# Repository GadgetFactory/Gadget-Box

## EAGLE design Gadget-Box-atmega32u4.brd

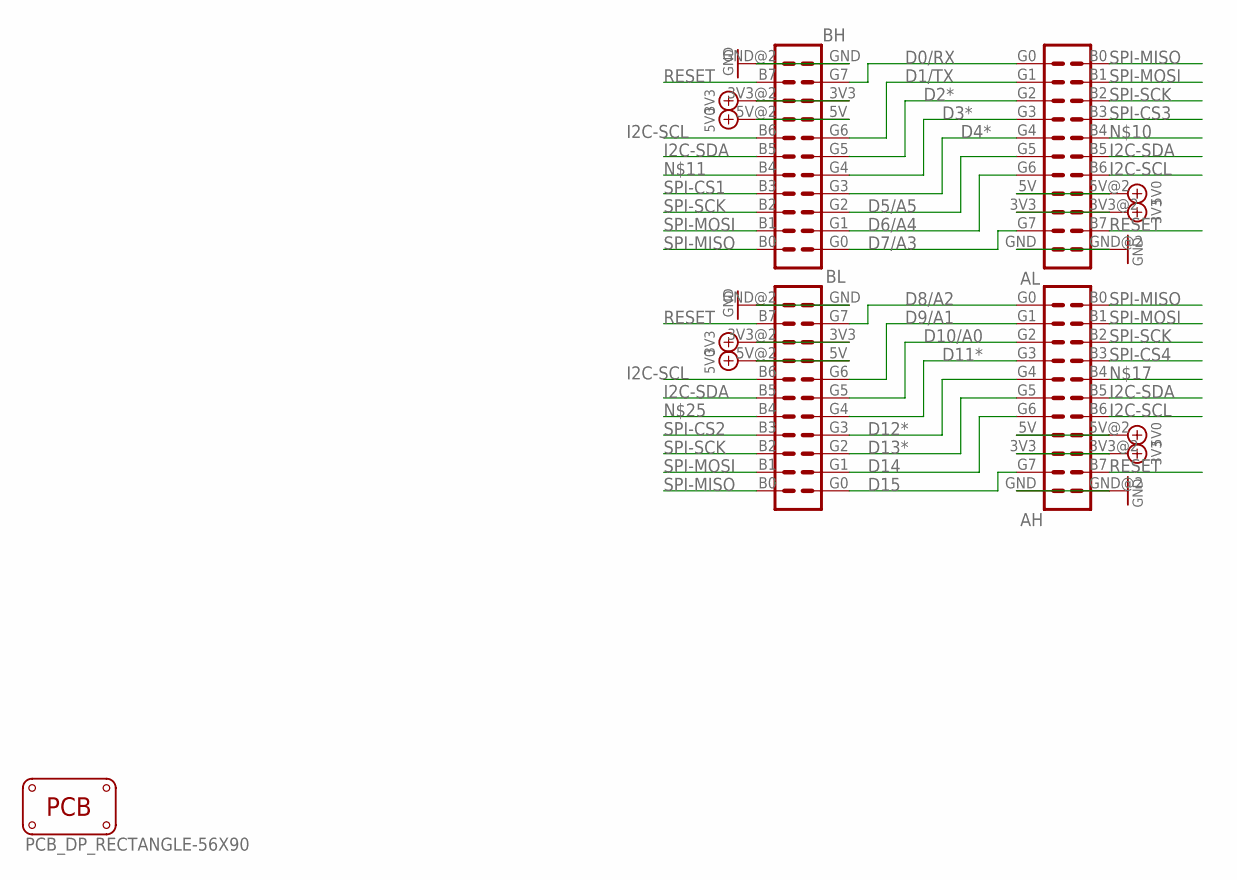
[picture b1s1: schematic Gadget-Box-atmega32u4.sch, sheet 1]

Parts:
AH: ECOGECOG_SLOT; ECOG
AL: ECOGECOG_SLOT; ECOG
BH: ECOGECOG_SLOT; ECOG
BL: ECOGECOG_SLOT; ECOG
PCB1: PCB_DP_RECTANGLE-56X90; DP9056_V1

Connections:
3V3: AH.3V3, AH.3V3@2 (3V3), AL.3V3, AL.3V3@2 (3V3), BH.3V3, BH.3V3@2 (3V3), BL.3V3, BL.3V3@2 (3V3); also elsewhere on the board
5V0: AH.5V, AH.5V@2 (5V), AL.5V, AL.5V@2 (5V), BH.5V, BH.5V@2 (5V), BL.5V, BL.5V@2 (5V); also elsewhere on the board
D0/RX: AL.G0, BH.G7; also elsewhere on the board
D1/TX: AL.G1, BH.G6; also elsewhere on the board
D2*: AL.G2, BH.G5; also elsewhere on the board
D3*: AL.G3, BH.G4; also elsewhere on the board
D4*: AL.G4, BH.G3; also elsewhere on the board
D5/A5: AL.G5, BH.G2; also elsewhere on the board
D6/A4: AL.G6, BH.G1; also elsewhere on the board
D7/A3: AL.G7, BH.G0; also elsewhere on the board
D8/A2: AH.G0, BL.G7; also elsewhere on the board
D9/A1: AH.G1, BL.G6; also elsewhere on the board
D10/A0: AH.G2, BL.G5; also elsewhere on the board
D11*: AH.G3, BL.G4; also elsewhere on the board
D12*: AH.G4, BL.G3; also elsewhere on the board
D13*: AH.G5, BL.G2; also elsewhere on the board
D14: AH.G6, BL.G1; also elsewhere on the board
D15: AH.G7, BL.G0; also elsewhere on the board
GND: AH.GND, AH.GND@2 (GND), AL.GND, AL.GND@2 (GND), BH.GND, BH.GND@2 (GND), BL.GND, BL.GND@2 (GND); also elsewhere on the board
I2C-SCL: AH.B6, AL.B6, BH.B6, BL.B6; also elsewhere on the board
I2C-SDA: AH.B5, AL.B5, BH.B5, BL.B5; also elsewhere on the board
RESET: AH.B7, AL.B7, BH.B7, BL.B7; also elsewhere on the board
SPI-CS1: BH.B3; also elsewhere on the board
SPI-CS2: BL.B3; also elsewhere on the board
SPI-CS3: AL.B3; also elsewhere on the board
SPI-CS4: AH.B3; also elsewhere on the board
SPI-MISO: AH.B0, AL.B0, BH.B0, BL.B0; also elsewhere on the board
SPI-MOSI: AH.B1, AL.B1, BH.B1, BL.B1; also elsewhere on the board
SPI-SCK: AH.B2, AL.B2, BH.B2, BL.B2; also elsewhere on the board

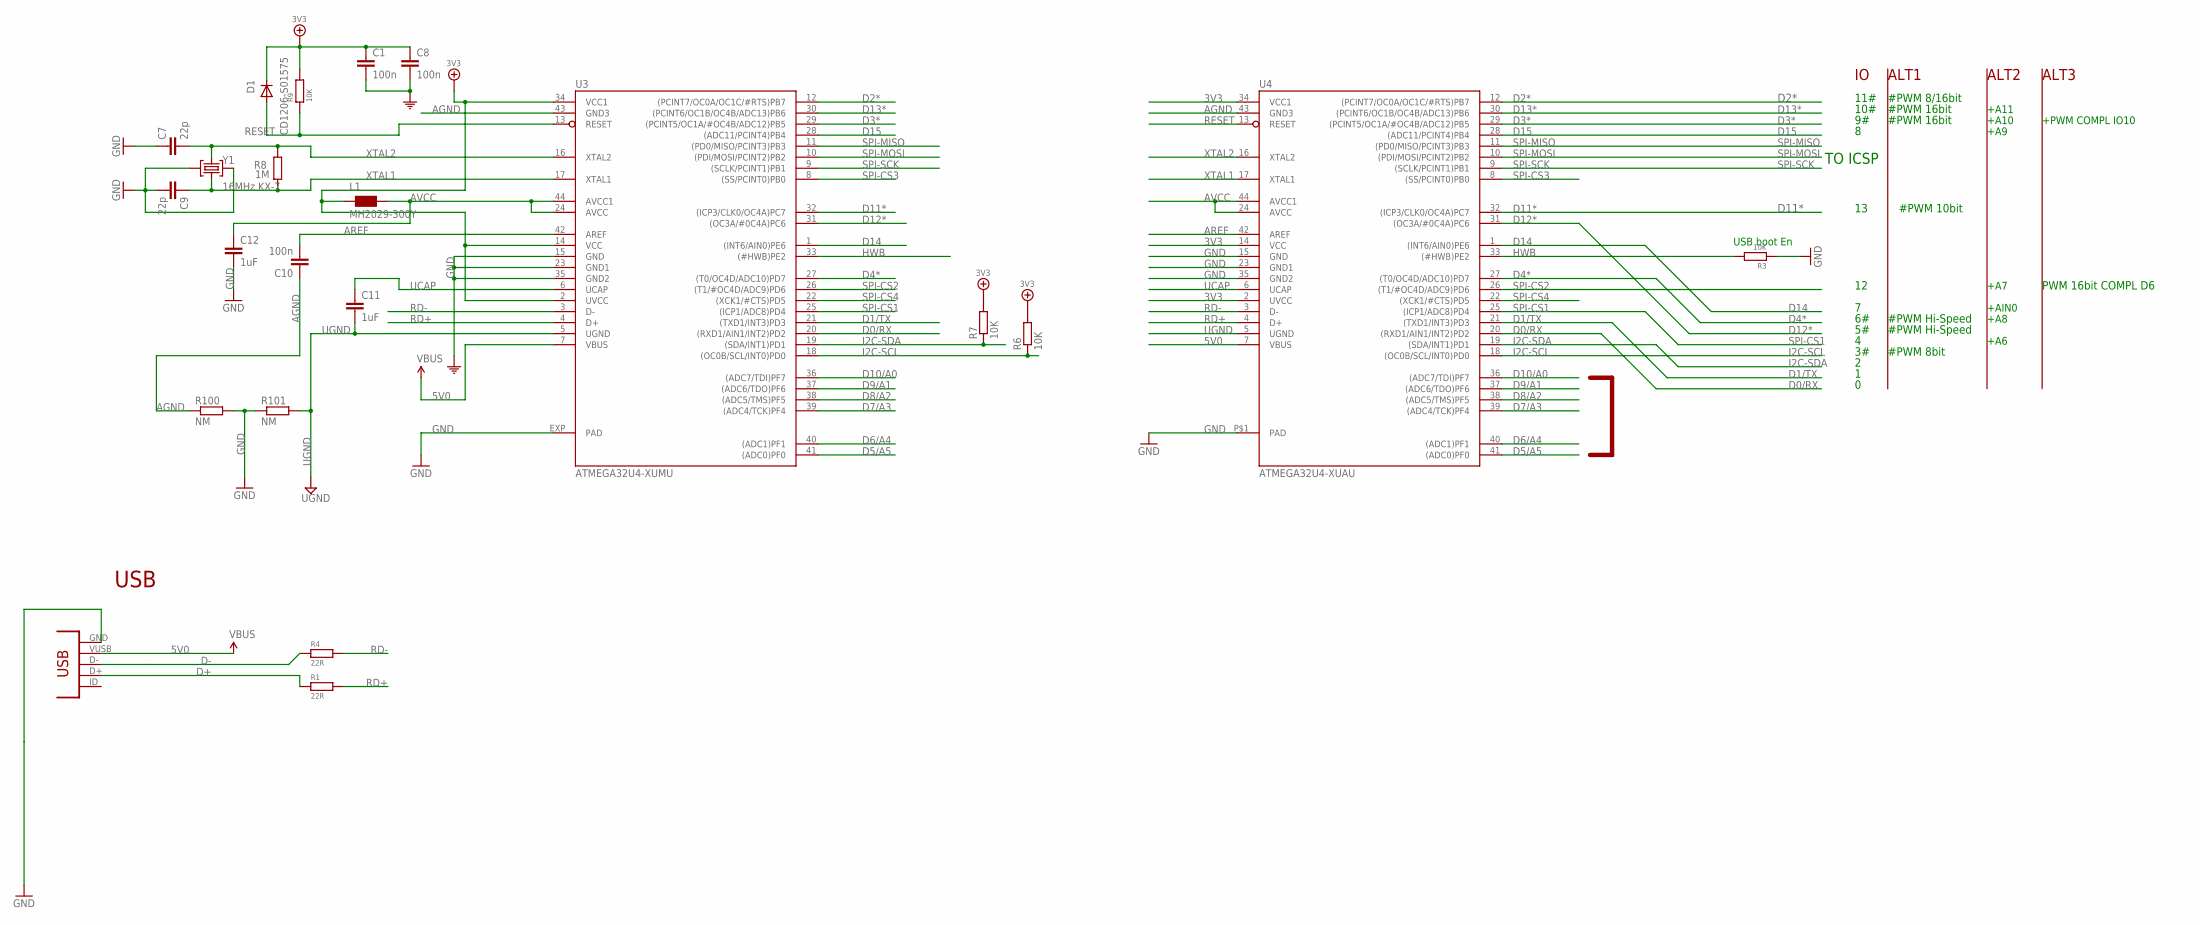
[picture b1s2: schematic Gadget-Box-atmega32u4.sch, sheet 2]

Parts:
C1, C8, C10: 100n; C0603-ROUND
C7, C9: 22p; C0603-ROUND
C11, C12: 1uF; C0603-ROUND
D1: CD1206-S01575; MINIMELF
L1: MH2029-300Y; 0805
R1, R4: 22R; 0805
R3, R9: 10K; 0805
R6, R7: 10K; R0402
R8: 1M; R0603-ROUND
R100, R101: NM; R0402
U3: ATMEGA32U4-XUMU; QFN44ML7X7
U4: ATMEGA32U4-XUAU; TQFP44-PAD
USB: CONN_USB; CONN_USB_MINI-B
Y1: 16MHz KX-7; CRYSTAL-3.2-2.5

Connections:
3V3: C1.1, C8.1, D1.C, L1.1, R6.2, R7.2, R9.2, U3.2 (UVCC), U3.14 (VCC), U3.34 (VCC1), U4.2 (UVCC), U4.14 (VCC), U4.34 (VCC1); also elsewhere on the board
5V0: U3.7 (VBUS), U4.7 (VBUS), USB.VUSB; also elsewhere on the board
AGND: C10.1, R100.1, U3.43 (GND3), U4.43 (GND3)
AREF: C10.2, U3.42 (AREF), U4.42 (AREF)
AVCC: C12.1, L1.2, U3.24 (AVCC), U3.44 (AVCC1), U4.24 (AVCC), U4.44 (AVCC1)
D0/RX: U3.20 ((RXD1/AIN1/INT2)PD2), U4.20 ((RXD1/AIN1/INT2)PD2); also elsewhere on the board
D1/TX: U3.21 ((TXD1/INT3)PD3), U4.21 ((TXD1/INT3)PD3); also elsewhere on the board
D2*: U3.12 ((PCINT7/OC0A/OC1C/#RTS)PB7), U4.12 ((PCINT7/OC0A/OC1C/#RTS)PB7); also elsewhere on the board
D3*: U3.29 ((PCINT5/OC1A/#OC4B/ADC12)PB5), U4.29 ((PCINT5/OC1A/#OC4B/ADC12)PB5); also elsewhere on the board
D4*: U3.27 ((T0/OC4D/ADC10)PD7), U4.27 ((T0/OC4D/ADC10)PD7); also elsewhere on the board
D5/A5: U3.41 ((ADC0)PF0), U4.41 ((ADC0)PF0); also elsewhere on the board
D6/A4: U3.40 ((ADC1)PF1), U4.40 ((ADC1)PF1); also elsewhere on the board
D7/A3: U3.39 ((ADC4/TCK)PF4), U4.39 ((ADC4/TCK)PF4); also elsewhere on the board
D8/A2: U3.38 ((ADC5/TMS)PF5), U4.38 ((ADC5/TMS)PF5); also elsewhere on the board
D9/A1: U3.37 ((ADC6/TDO)PF6), U4.37 ((ADC6/TDO)PF6); also elsewhere on the board
D10/A0: U3.36 ((ADC7/TDI)PF7), U4.36 ((ADC7/TDI)PF7); also elsewhere on the board
D11*: U3.32 ((ICP3/CLK0/OC4A)PC7), U4.32 ((ICP3/CLK0/OC4A)PC7); also elsewhere on the board
D12*: U3.31 ((OC3A/#0C4A)PC6), U4.31 ((OC3A/#0C4A)PC6); also elsewhere on the board
D13*: U3.30 ((PCINT6/OC1B/OC4B/ADC13)PB6), U4.30 ((PCINT6/OC1B/OC4B/ADC13)PB6); also elsewhere on the board
D14: U3.1 ((INT6/AIN0)PE6), U4.1 ((INT6/AIN0)PE6); also elsewhere on the board
D15: U3.28 ((ADC11/PCINT4)PB4), U4.28 ((ADC11/PCINT4)PB4); also elsewhere on the board
D+: R1.1, USB.D+
D-: R4.1, USB.D-
GND: C1.2, C7.1, C8.2, C9.2, C12.2, R3.1, R100.2, R101.1, U3.15 (GND), U3.23 (GND1), U3.35 (GND2), U3.EXP (PAD), U4.15 (GND), U4.23 (GND1), U4.35 (GND2), U4.P$1 (PAD), USB.GND, Y1.2 (GND), Y1.4 (GND); also elsewhere on the board
HWB: R3.2, U3.33 ((#HWB)PE2), U4.33 ((#HWB)PE2)
I2C-SCL: R6.1, U3.18 ((OC0B/SCL/INT0)PD0), U4.18 ((OC0B/SCL/INT0)PD0); also elsewhere on the board
I2C-SDA: R7.1, U3.19 ((SDA/INT1)PD1), U4.19 ((SDA/INT1)PD1); also elsewhere on the board
RD+: R1.2, U3.4 (D+), U4.4 (D+)
RD-: R4.2, U3.3 (D-), U4.3 (D-)
RESET: D1.A, R9.1, U3.13 (RESET), U4.13 (RESET); also elsewhere on the board
SPI-CS1: U3.25 ((ICP1/ADC8)PD4), U4.25 ((ICP1/ADC8)PD4); also elsewhere on the board
SPI-CS2: U3.26 ((T1/#OC4D/ADC9)PD6), U4.26 ((T1/#OC4D/ADC9)PD6); also elsewhere on the board
SPI-CS3: U3.8 ((SS/PCINT0)PB0), U4.8 ((SS/PCINT0)PB0); also elsewhere on the board
SPI-CS4: U3.22 ((XCK1/#CTS)PD5), U4.22 ((XCK1/#CTS)PD5); also elsewhere on the board
SPI-MISO: U3.11 ((PD0/MISO/PCINT3)PB3), U4.11 ((PD0/MISO/PCINT3)PB3); also elsewhere on the board
SPI-MOSI: U3.10 ((PDI/MOSI/PCINT2)PB2), U4.10 ((PDI/MOSI/PCINT2)PB2); also elsewhere on the board
SPI-SCK: U3.9 ((SCLK/PCINT1)PB1), U4.9 ((SCLK/PCINT1)PB1); also elsewhere on the board
UCAP: C11.1, U3.6 (UCAP), U4.6 (UCAP)
UGND: C11.2, R101.2, U3.5 (UGND), U4.5 (UGND)
XTAL1: C9.1, R8.1, U3.17 (XTAL1), U4.17 (XTAL1), Y1.1 (C1)
XTAL2: C7.2, R8.2, U3.16 (XTAL2), U4.16 (XTAL2), Y1.3 (C2)

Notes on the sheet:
USB boot En
USB
TO ICSP
10#
11#
#PWM 8bit
#PWM Hi-Speed
#PWM 8/16bit
#PWM 16bit
PWM 16bit COMPL D6
#PWM 10bit
+A6
+A7
+A11
+A10
+A8
+A9
+PWM COMPL IO10
+AIN0
ALT1
ALT2
ALT3

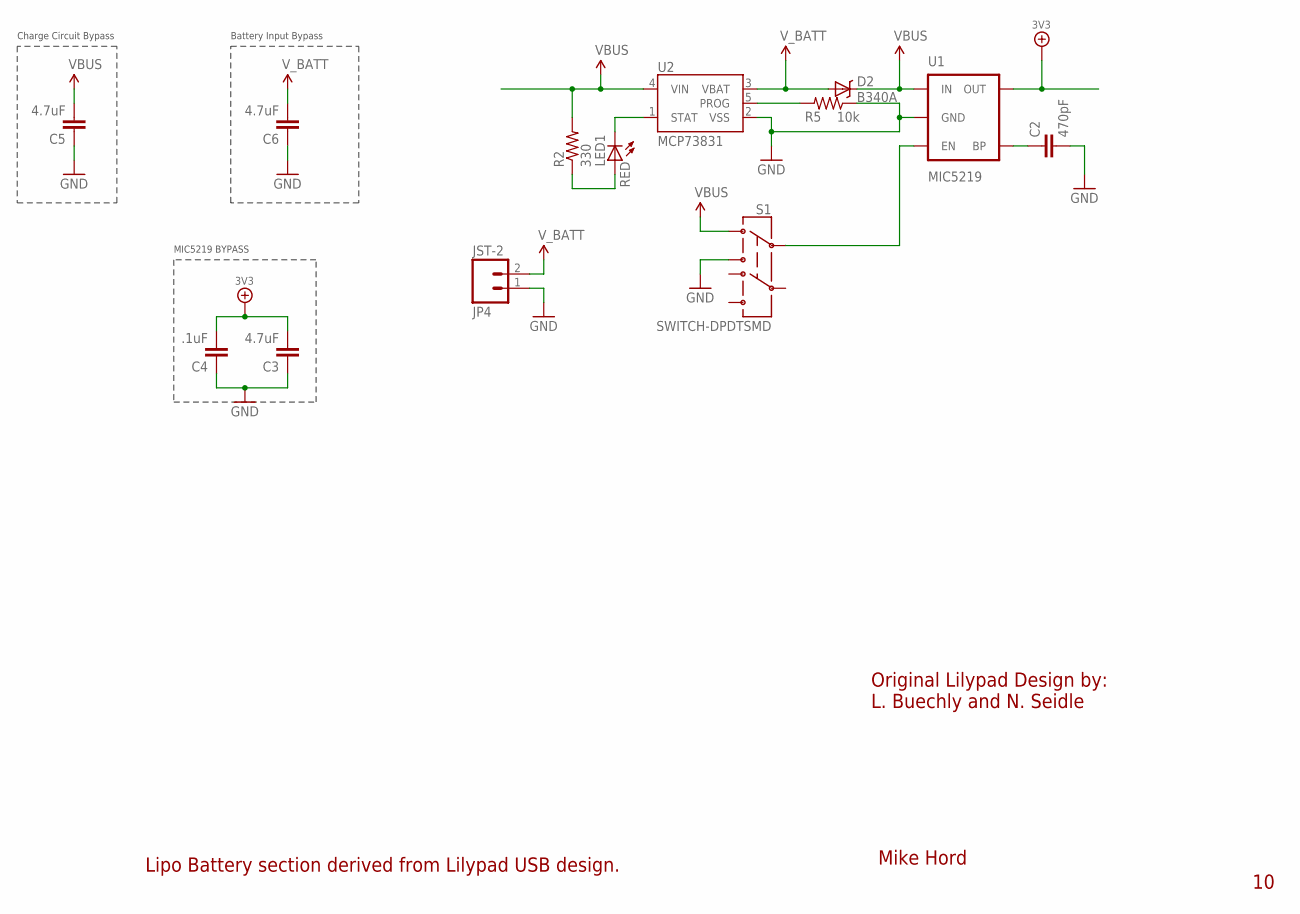
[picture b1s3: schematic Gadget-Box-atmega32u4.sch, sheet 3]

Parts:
C2: 470pF; 0603-CAP
C3: 4.7uF; 0603-CAP
C4: .1uF; 0603-CAP
C5, C6: 4.7uF; 1206
D2: B340A; SMA-DIODE
JP4: JST-2; JST-2-SMD
LED1: RED; LED-0603
R2: 330; 0603-RES
R5: 10k; 0603-RES
S1: SWITCH-DPDTSMD; AYZ0202
U1: MIC5219; SOT23-5
U2: MCP73831; SOT23-5

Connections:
3V3: C3.2, C4.2, U1.5 (OUT); also elsewhere on the board
5V0: C5.2, D2.C, R2.2, S1.1, U1.1 (IN), U2.4 (VIN); also elsewhere on the board
GND: C2.2, C3.1, C4.1, C5.1, C6.1, JP4.1 (2), R5.1, S1.3, U1.2 (GND), U2.2 (VSS); also elsewhere on the board
unnamed: S1.2, U1.3 (EN)
unnamed: LED1.A, R2.1
unnamed: LED1.C, U2.1 (STAT)
unnamed: R5.2, U2.5 (PROG)
unnamed: C2.1, U1.4 (BP)
V_BATT: C6.2, D2.A, JP4.2 (1), U2.3 (VBAT)

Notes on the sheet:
MIC5219 BYPASS
Mike Hord
Original Lilypad Design by:
L. Buechly and N. Seidle
Charge Circuit Bypass
Battery Input Bypass
Lipo Battery section derived from Lilypad USB design.

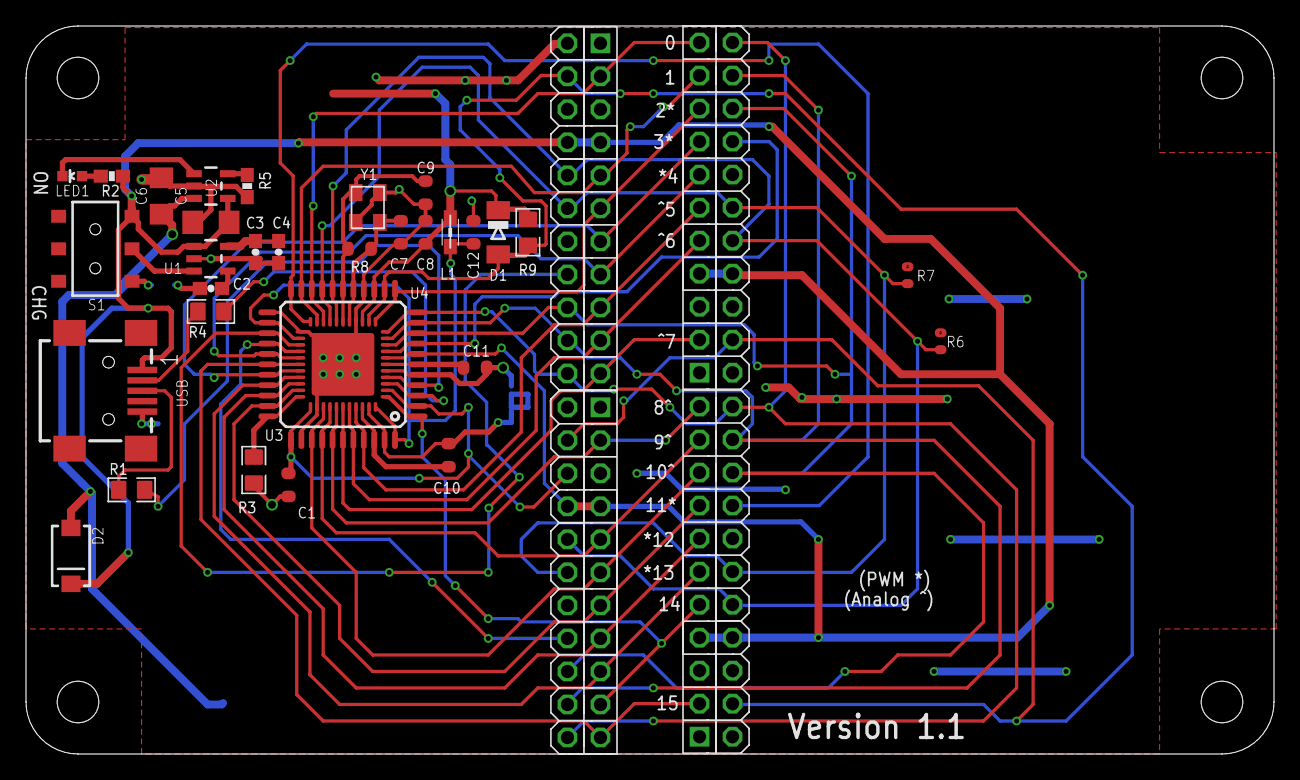
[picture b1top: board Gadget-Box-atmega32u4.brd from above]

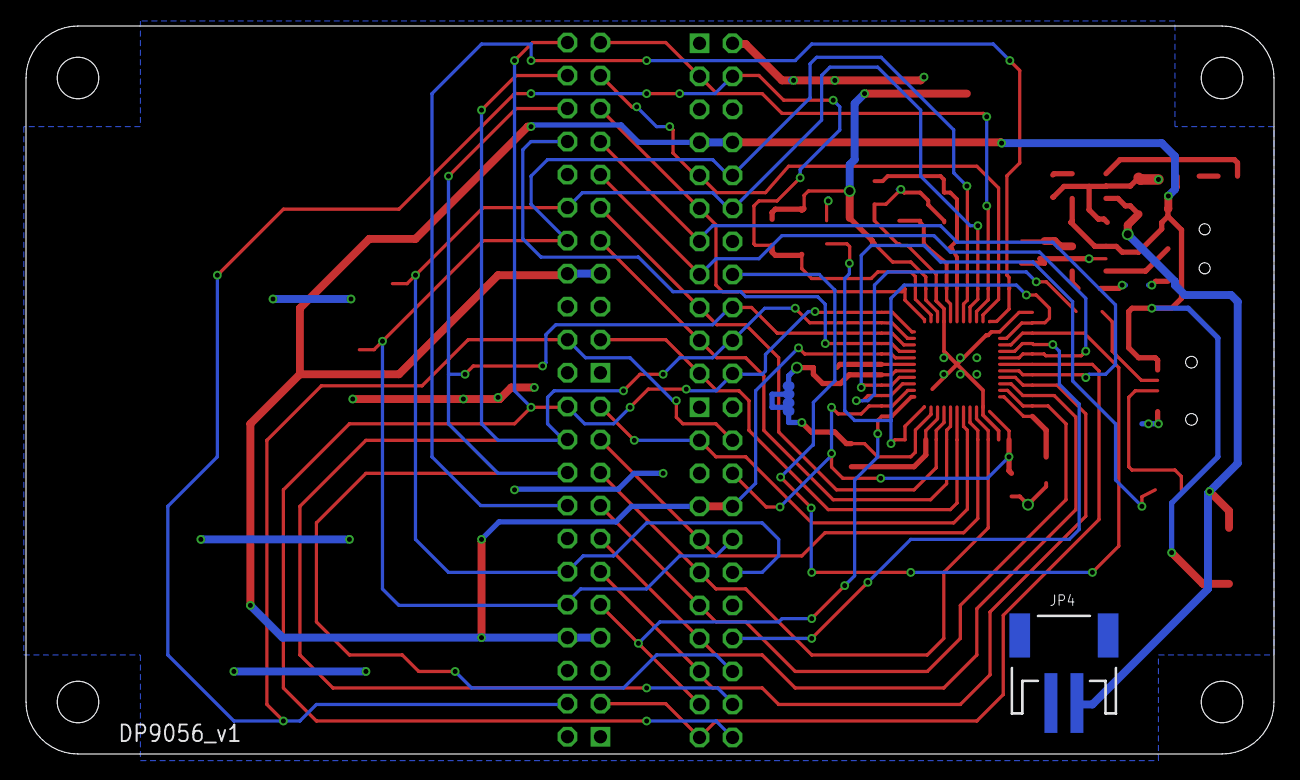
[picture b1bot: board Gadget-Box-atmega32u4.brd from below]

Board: 2 copper layers, 96.0 x 56.0 mm, 40 parts (3 on the bottom side), 47 nets.

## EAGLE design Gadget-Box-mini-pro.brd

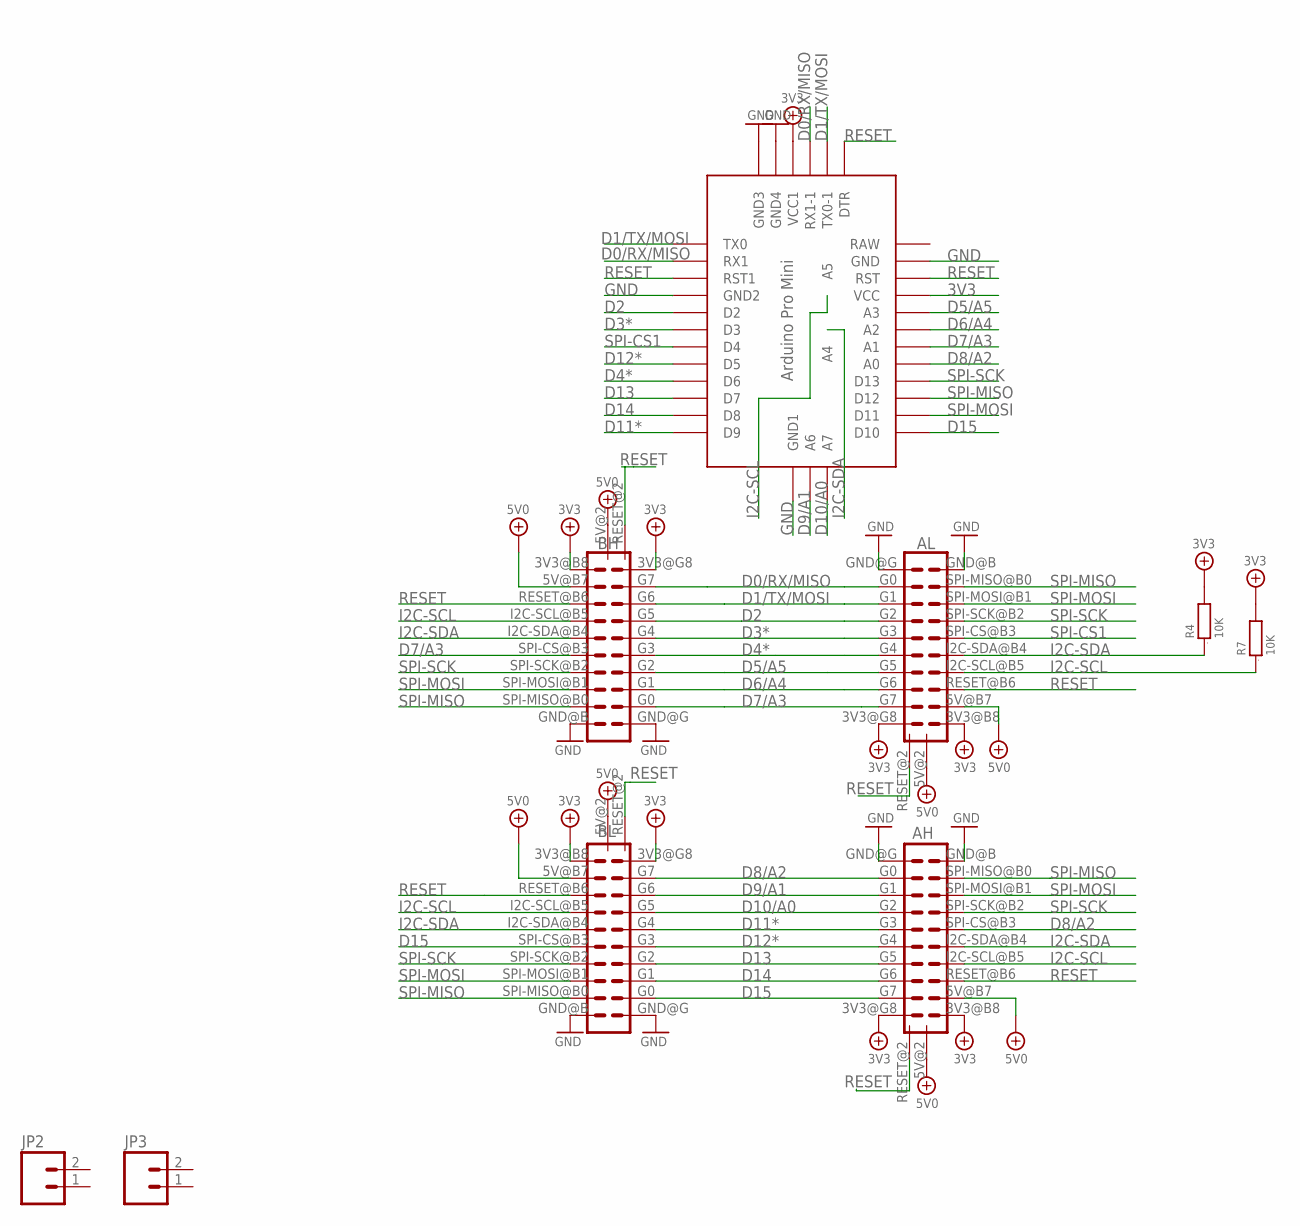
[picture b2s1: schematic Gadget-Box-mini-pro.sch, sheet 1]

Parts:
AH: ECOGECOG_SLOT_ALT1; ECOG_ALT1; PARTNO PPPC102LFBN-RC,SULLINS CONNECTOR SOLUTI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
AL: ECOGECOG_SLOT_ALT1; ECOG_ALT1; PARTNO PPPC102LFBN-RC,SULLINS CONNECTOR SOLUTI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
BH: ECOGECOG_SLOT_ALT1; ECOG_ALT1; PARTNO PPPC102LFBN-RC,SULLINS CONNECTOR SOLUTI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
BL: ECOGECOG_SLOT_ALT1; ECOG_ALT1; PARTNO PPPC102LFBN-RC,SULLINS CONNECTOR SOLUTI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
JP2, JP3: M021X02_NO_SILK; 1X02_NO_SILK
R4, R7: 10K; 0805
U$1: ABK-PRO-MINI

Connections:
3V3: AH.3V3@B8 (3V3), AH.3V3@G8 (3V3), AL.3V3@B8 (3V3), AL.3V3@G8 (3V3), BH.3V3@B8 (3V3), BH.3V3@G8 (3V3), BL.3V3@B8 (3V3), BL.3V3@G8 (3V3), R4.2, R7.2, U$1.VCC, U$1.VCC1; also elsewhere on the board
5V0: AH.5V@2 (5V), AH.5V@B7 (5V), AL.5V@2 (5V), AL.5V@B7 (5V), BH.5V@2 (5V), BH.5V@B7 (5V), BL.5V@2 (5V), BL.5V@B7 (5V); also elsewhere on the board
D0/RX/MISO: AL.G0, BH.G7, U$1.RX1, U$1.RX1-1
D1/TX/MOSI: AL.G1, BH.G6, U$1.TX0, U$1.TX0-1
D2: AL.G2, BH.G5, U$1.D2
D3*: AL.G3, BH.G4, U$1.D3
D4*: AL.G4, BH.G3, U$1.D6
D5/A5: AL.G5, BH.G2, U$1.A3; also elsewhere on the board
D6/A4: AL.G6, BH.G1, U$1.A2
D7/A3: AL.G7, BH.G0, BH.SPI-CS@B3 (SPI-CS), U$1.A1
D8/A2: AH.G0, AH.SPI-CS@B3 (SPI-CS), BL.G7, U$1.A0
D9/A1: AH.G1, BL.G6, U$1.A6
D10/A0: AH.G2, BL.G5, U$1.A7
D11*: AH.G3, BL.G4, U$1.D9
D12*: AH.G4, BL.G3, U$1.D5
D13: AH.G5, BL.G2, U$1.D7
D14: AH.G6, BL.G1, U$1.D8
D15: AH.G7, BL.G0, BL.SPI-CS@B3 (SPI-CS), U$1.D10
GND: AH.GND@B (GND), AH.GND@G (GND), AL.GND@B (GND), AL.GND@G (GND), BH.GND@B (GND), BH.GND@G (GND), BL.GND@B (GND), BL.GND@G (GND), U$1.GND, U$1.GND1 (GND2), U$1.GND2 (GND3), U$1.GND3 (GND4), U$1.GND4 (GND1); also elsewhere on the board
I2C-SCL: AH.I2C-SCL@B5 (I2C-SCL), AL.I2C-SCL@B5 (I2C-SCL), BH.I2C-SCL@B5 (I2C-SCL), BL.I2C-SCL@B5 (I2C-SCL), R7.1, U$1.A5
I2C-SDA: AH.I2C-SDA@B4 (I2C-SDA), AL.I2C-SDA@B4 (I2C-SDA), BH.I2C-SDA@B4 (I2C-SDA), BL.I2C-SDA@B4 (I2C-SDA), R4.1, U$1.A4
RESET: AH.RESET@2 (RESET), AH.RESET@B6 (RESET), AL.RESET@2 (RESET), AL.RESET@B6 (RESET), BH.RESET@2 (RESET), BH.RESET@B6 (RESET), BL.RESET@2 (RESET), BL.RESET@B6 (RESET), U$1.DTR, U$1.RST, U$1.RST1
SPI-CS1: AL.SPI-CS@B3 (SPI-CS), U$1.D4
SPI-MISO: AH.SPI-MISO@B0 (SPI-MISO), AL.SPI-MISO@B0 (SPI-MISO), BH.SPI-MISO@B0 (SPI-MISO), BL.SPI-MISO@B0 (SPI-MISO), U$1.D12
SPI-MOSI: AH.SPI-MOSI@B1 (SPI-MOSI), AL.SPI-MOSI@B1 (SPI-MOSI), BH.SPI-MOSI@B1 (SPI-MOSI), BL.SPI-MOSI@B1 (SPI-MOSI), U$1.D11
SPI-SCK: AH.SPI-SCK@B2 (SPI-SCK), AL.SPI-SCK@B2 (SPI-SCK), BH.SPI-SCK@B2 (SPI-SCK), BL.SPI-SCK@B2 (SPI-SCK), U$1.D13

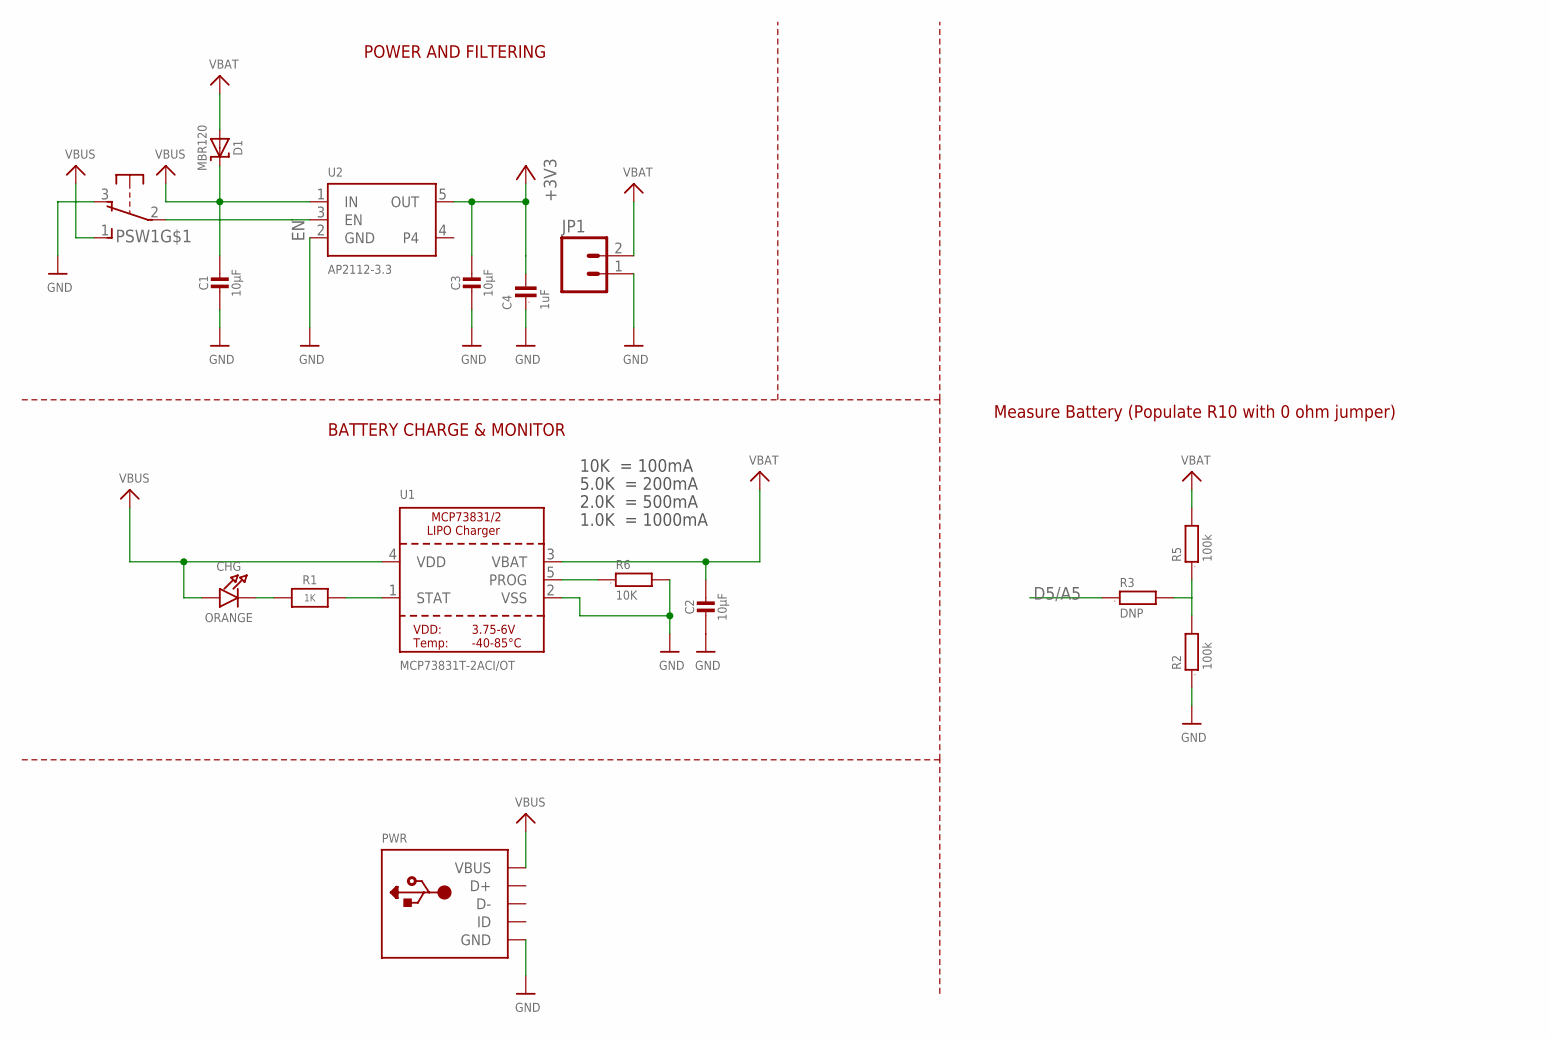
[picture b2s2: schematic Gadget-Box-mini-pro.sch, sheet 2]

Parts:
C1, C2, C3: 10µF; 0805-NO; PARTNO CL21F106ZPFNNNE,Samsung,DK,1276-3012-1-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
C4: 1uF; 0603; PARTNO C1608X5R1A105K080AC,TDK CORPORATION (VA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
CHG: ORANGE; CHIPLED_0805_NOOUTLINE; PARTNO LTST-C171EKT,LITE-ON INC (VA),DK,160-14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
D1: MBR120; SOD-123; PARTNO MBR120VLSFT3G,on semiconductor,dk,MBR12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
JP1: M02-JST-2-PTH-NO_SILK; JST-2-PTH-NS
PSW1: OS102011MA1Q; PARTNO OS102011MA1QN1,C&K Components,dk,CKN955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
PWR: USBMINIB; USB-MINIB
R1: 1K; 0603-NO; PARTNO RC0603JR-071KL,YAGEO (VA),dk,311-1.0KGR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
R2, R5: 100k; 0603; PARTNO RC0603JR-07100KL,YAGEO (VA),dk,311-100K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
R3: DNP; 0603
R6: 10K; 0603; PARTNO RC0603JR-0710KL,YAGEO (VA),dk,311-10KGR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
U1: MCP73831T-2ACI/OT; SOT23-5; PARTNO MCP73831T-2ACI/OT,MICROCHIP TECHNOLOGY 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
U2: AP2112-3.3; SOT23-5; PARTNO AP2112K-3.3TRG1,Diodes Incorporated,dk,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

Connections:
3V3: C3.1, C4.2, U2.5 (OUT); also elsewhere on the board
5V0: C1.1, CHG.A, D1.C, PSW1.1 (S), PWR.VBUS, U1.4 (VDD), U2.1 (IN); also elsewhere on the board
D5/A5: R3.1; also elsewhere on the board
EN: PSW1.2, U2.3 (EN)
GND: C1.2, C2.2, C3.2, C4.1, JP1.1, PSW1.3 (O), PWR.GND, R2.1, R6.2, U1.2 (VSS), U2.2 (GND); also elsewhere on the board
unnamed: CHG.C, R1.1
unnamed: R2.2, R3.2, R5.1
unnamed: R1.2, U1.1 (STAT)
unnamed: R6.1, U1.5 (PROG)
VBAT: C2.1, D1.A, JP1.2, R5.2, U1.3 (VBAT)

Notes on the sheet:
POWER AND FILTERING
10K = 100mA
5.0K = 200mA
2.0K = 500mA
1.0K = 1000mA
BATTERY CHARGE & MONITOR
Measure Battery (Populate R10 with 0 ohm jumper)

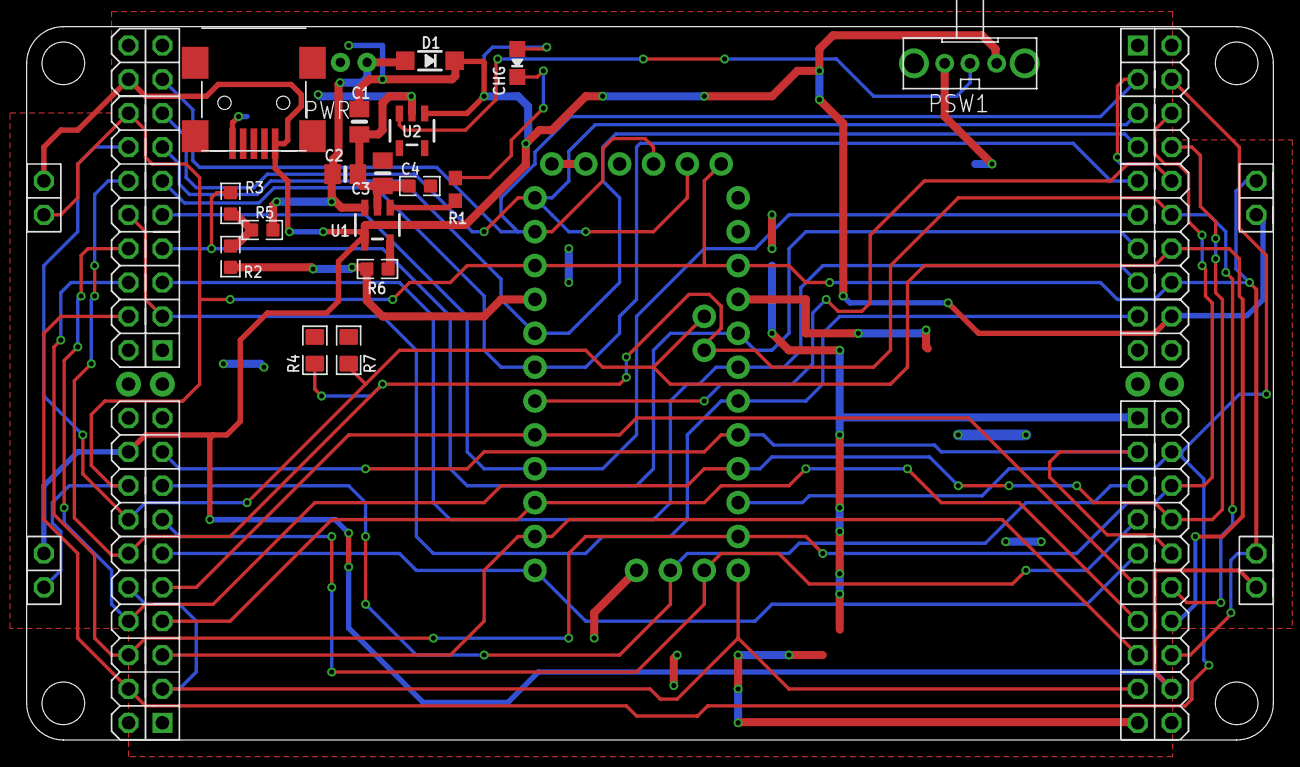
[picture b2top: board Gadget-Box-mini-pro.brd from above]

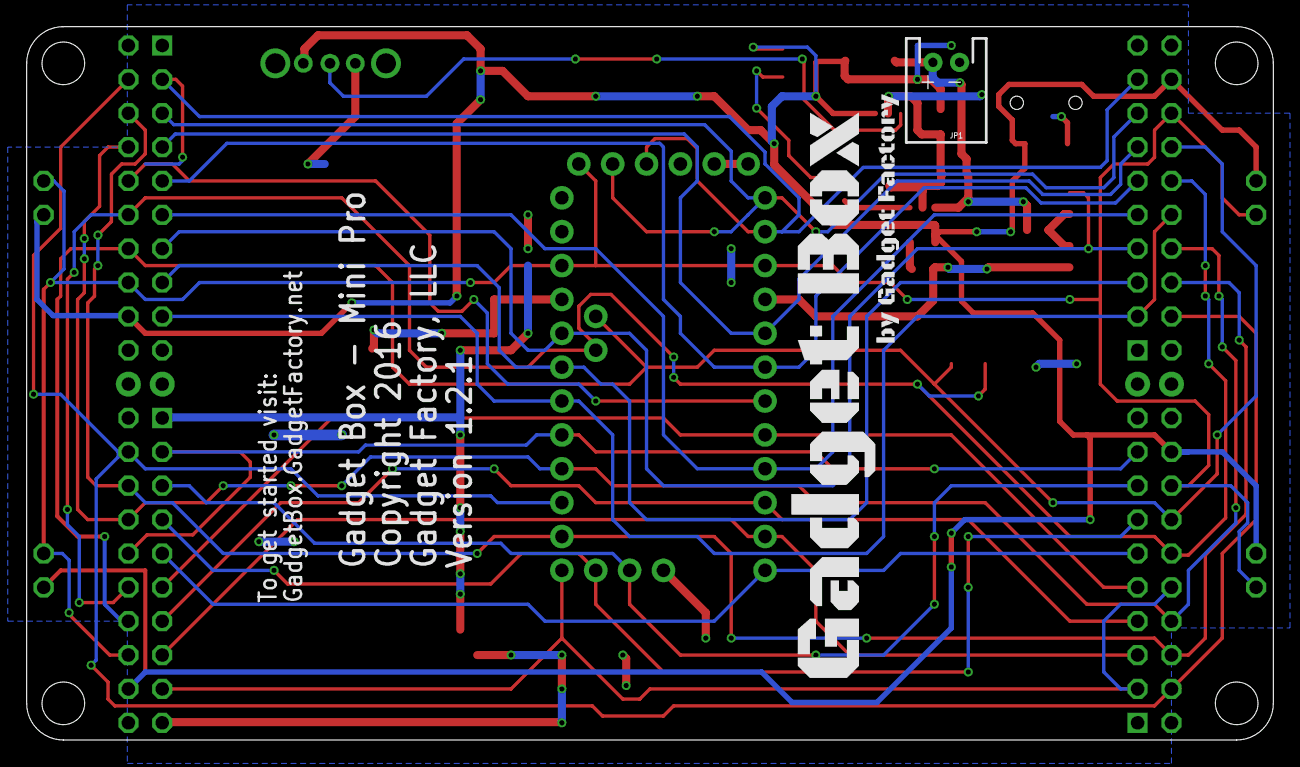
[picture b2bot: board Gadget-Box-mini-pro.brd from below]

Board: 2 copper layers, 93.5 x 53.5 mm, 27 parts (2 on the bottom side), 32 nets.

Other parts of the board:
$$U$1: ECOG93P53P5
U$100: GADGETBOX_TEXT

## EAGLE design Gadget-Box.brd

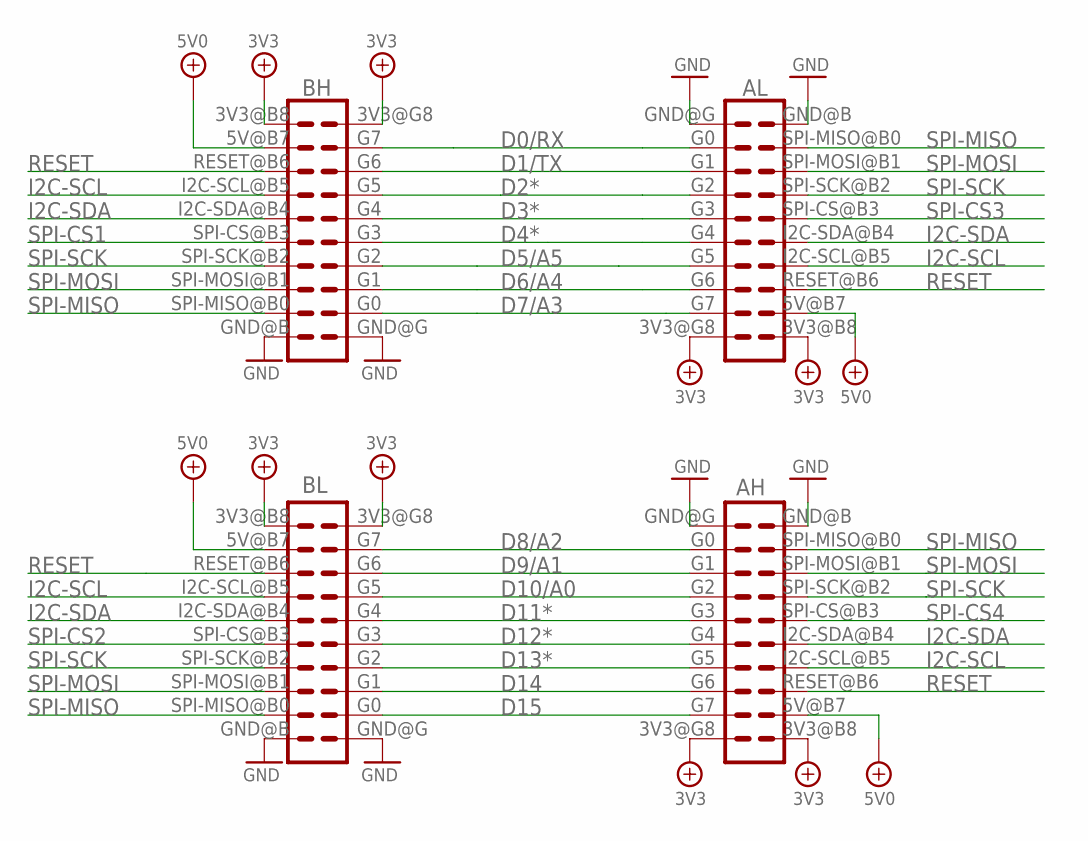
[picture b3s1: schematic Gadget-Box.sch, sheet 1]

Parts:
AH: ECOGECOG_SLOT; ECOG; PARTNO PPPC102LFBN-RC,SULLINS CONNECTOR SOLUTI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
AL: ECOGECOG_SLOT; ECOG; PARTNO PPPC102LFBN-RC,SULLINS CONNECTOR SOLUTI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
BH: ECOGECOG_SLOT; ECOG; PARTNO PPPC102LFBN-RC,SULLINS CONNECTOR SOLUTI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
BL: ECOGECOG_SLOT; ECOG; PARTNO PPPC102LFBN-RC,SULLINS CONNECTOR SOLUTI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

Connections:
3V3: AH.3V3@B8 (3V3), AH.3V3@G8 (3V3), AL.3V3@B8 (3V3), AL.3V3@G8 (3V3), BH.3V3@B8 (3V3), BH.3V3@G8 (3V3), BL.3V3@B8 (3V3), BL.3V3@G8 (3V3); also elsewhere on the board
D0/RX: AL.G0, BH.G7; also elsewhere on the board
D1/TX: AL.G1, BH.G6; also elsewhere on the board
D2*: AL.G2, BH.G5; also elsewhere on the board
D3*: AL.G3, BH.G4; also elsewhere on the board
D4*: AL.G4, BH.G3; also elsewhere on the board
D5/A5: AL.G5, BH.G2; also elsewhere on the board
D6/A4: AL.G6, BH.G1; also elsewhere on the board
D7/A3: AL.G7, BH.G0; also elsewhere on the board
D8/A2: AH.G0, BL.G7; also elsewhere on the board
D9/A1: AH.G1, BL.G6; also elsewhere on the board
D10/A0: AH.G2, BL.G5; also elsewhere on the board
D11*: AH.G3, BL.G4; also elsewhere on the board
D12*: AH.G4, BL.G3; also elsewhere on the board
D13*: AH.G5, BL.G2; also elsewhere on the board
D14: AH.G6, BL.G1; also elsewhere on the board
D15: AH.G7, BL.G0; also elsewhere on the board
GND: AH.GND@B (GND), AH.GND@G (GND), AL.GND@B (GND), AL.GND@G (GND), BH.GND@B (GND), BH.GND@G (GND), BL.GND@B (GND), BL.GND@G (GND); also elsewhere on the board
I2C-SCL: AH.I2C-SCL@B5 (I2C-SCL), AL.I2C-SCL@B5 (I2C-SCL), BH.I2C-SCL@B5 (I2C-SCL), BL.I2C-SCL@B5 (I2C-SCL); also elsewhere on the board
I2C-SDA: AH.I2C-SDA@B4 (I2C-SDA), AL.I2C-SDA@B4 (I2C-SDA), BH.I2C-SDA@B4 (I2C-SDA), BL.I2C-SDA@B4 (I2C-SDA); also elsewhere on the board
RESET: AH.RESET@B6 (RESET), AL.RESET@B6 (RESET), BH.RESET@B6 (RESET), BL.RESET@B6 (RESET); also elsewhere on the board
SPI-CS1: BH.SPI-CS@B3 (SPI-CS); also elsewhere on the board
SPI-CS2: BL.SPI-CS@B3 (SPI-CS); also elsewhere on the board
SPI-CS3: AL.SPI-CS@B3 (SPI-CS); also elsewhere on the board
SPI-CS4: AH.SPI-CS@B3 (SPI-CS); also elsewhere on the board
SPI-MISO: AH.SPI-MISO@B0 (SPI-MISO), AL.SPI-MISO@B0 (SPI-MISO), BH.SPI-MISO@B0 (SPI-MISO), BL.SPI-MISO@B0 (SPI-MISO); also elsewhere on the board
SPI-MOSI: AH.SPI-MOSI@B1 (SPI-MOSI), AL.SPI-MOSI@B1 (SPI-MOSI), BH.SPI-MOSI@B1 (SPI-MOSI), BL.SPI-MOSI@B1 (SPI-MOSI); also elsewhere on the board
SPI-SCK: AH.SPI-SCK@B2 (SPI-SCK), AL.SPI-SCK@B2 (SPI-SCK), BH.SPI-SCK@B2 (SPI-SCK), BL.SPI-SCK@B2 (SPI-SCK); also elsewhere on the board
VBUS: AH.5V@B7 (5V), AL.5V@B7 (5V), BH.5V@B7 (5V), BL.5V@B7 (5V); also elsewhere on the board

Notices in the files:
Gadget-Box-mini-pro.brd:
Copyright 2016
parts and their libraries:
SparkFun-PowerIC: Licensing: CC v3.0 Share-Alike You are welcome to use this library for commercial purposes.
SparkFun-Aesthetics: http://creativecommons.org/licenses/by-sa/3.0
